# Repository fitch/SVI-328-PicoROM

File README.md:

# SVI-328 PicoROM

## Overview

SVI-328 PicoROM is a ROM emulator for Spectravideo 328 which uses a [Raspberry Pico 2 W](https://www.raspberrypi.com/products/raspberry-pi-pico-2/) microcontroller board to emulate a SVI-328 game ROM cartridge.

Designed to integrate into the conventional cartridge slot of the SVI-328, this cartridge allows wireless transmission of ROM games from macOS/PC to the SVI-328 via Wi-Fi without any hardware modifications.

## Repository contents

This repository contains:

 - C firmware source code ([pico](pico/) directory) for Raspberry Pi Pico 2 W responsible for dynamic ROM emulation and wireless data transfer.
 - PCB design files ([pcb](pcb/) directory), including schematics and layouts, developed using KiCad, suitable for fabrication with, for example, [PCBWay](https://www.pcbway.com/).
 - Node.js JavaScript-based utility ([send_rom.js](js/send_rom.js)) designed for remote ROM image transmission via WiFi.
 - Z80 assembly language code ([rom](rom/) directory) constituting the boot-up ROM launcher, facilitating initial system configuration and operational initialization.

## How to get it running quickly

### Cartridge hardware

First, create the PCB by ordering it from [PCBWay](https://www.pcbway.com/) with the Gerber files provided in [release/svi-328-picorom-gerber.zip](release/svi-328-picorom-gerber.zip).

Then get a [Raspberry Pico 2 W](https://www.raspberrypi.com/products/raspberry-pi-pico-2/) (not the version 1, and make sure you order the Wi-Fi version W) and one atleast +5V diode (DigiKey part number 4878-1N4001CT-ND DIODE GEN PURP 50V 1A DO204AC works, for example).

Solder these together. :) 

### Cartridge software

Press Pico's BOOTSEL button (the only button on the board, see the board picture above) and while pressing plug it in to your computer via USB.

Then, find the UF2 flash binary file from [release/svi-328-picorom.uf2](release/svi-328-picorom.uf2).

Next, flash the Raspberry Pico 2 W by dragging the UF2 file on to the Pico USB drive and wait until Pico disconnects (displays `Disk Not Ejected Properly` in macOS) and the green LED light turns on to signal that the firmware booted correctly. Finally, remove the USB cable.

### Booting up and sending a ROM

Connect the cartridge to SVI-328 and boot it up. (Warning: **DO NOT** connect anything to the cartridge USB port when it is attached to the SVI-328. This will destroy the cartridge.)

If you didn't flash the Wi-Fi credentials (see section [Flashing Wi-Fi credentials to the cartridge](#flashing-wi-fi-credentials-to-the-cartridge)), the SVI-328 should ask for your Wi-Fi SSID and password. Please note, that once you store successfully working credentials, there is no way (currently) to remove the stored credentials using SVI-328. You need to use the command line utility described in section [Flashing Wi-Fi credentials to the cartridge](#flashing-wi-fi-credentials-to-the-cartridge).

The SVI-328 will remain waiting for a client.

To send a ROM from Windows or macOS, use the `send_rom.js` to send it. It should display the following information:
```
node js/send_rom.js Boulder\ Dash-MSX-to-SVI.rom 
Waiting for SVI-328 at address 0.0.0.0...
Connecting to SVI-328 at 192.168.1.100...
Connected. Sending ROM upload command...
ROM sent. Listening for logs:
```

After this, the SVI-328 should boot to the sent ROM.

**NOTE**: Only 32 kB ROM images are supported at the moment.

## System prerequisites

The replication and deployment of this project requires the following environment configurations:
 - Raspberry Pi Pico SDK installation and associated toolchains.
 - Node.js runtime environment for executing the provided WiFi-based ROM transmission scripts.
 - KiCad for PCB customization, schematic evaluation, and Gerber file generation.

The build scripts have been developed and tested with macOS Sonoma 14.6.1 and requires the following software to be installed:

 - [Visual Studio Code](https://code.visualstudio.com) 1.98.2 or newer 
 - Raspberry Pico Visual Studio Code extensions with [these](https://www.raspberrypi.com/news/get-started-with-raspberry-pi-pico-series-and-vs-code/) instructions
 - picotool 2.1.1, `brew install picotool` with [HomeBrew](https://brew.sh)
 - [z88dk version 2.3](https://github.com/z88dk/z88dk) (currently only z88dk-z80asm is used)
 - [openMSX emulator version 20.0](https://openmsx.org/) (which should be installed in /Applications/openMSX.app)
 - [Node.js version 22.12.10](https://nodejs.org/en) or newer
 - [Node Version Manager 22.12.0](https://github.com/nvm-sh/nvm) or newer (it's easier to manage Node versions with this, but you can omit this you install Node.js some other way)
 - [KiCad version 8.0.6](https://www.kicad.org/download/) or newer

## SVI-318 compatibility

The hardware will work with SVI-318 and the loader software should also work with it, altough it has not been tested on a real device yet.

## Compiling the source code

### The launcher ROM source code for SVI-328

The launcher ROM code is in [rom](rom/) directory and you can compile with the following commands:

```
nvm use
make production
```

This will create the ROM binary and the includable rom.h (for the next step) in `release` directory. Copy the `rom.h` to `pico` directory for the next step:

```
cp release/rom.h ../pico/
```

### Raspberry Pico 2 W firmware source code

The Pico firmware source code is located in [pico](pico/) directory and you can compile it by opening the folder in Visual Studio Code. First time, if you have installed the Visual Studio Code extensions, VSCode will install the Pico SDK and then you can click the `Compile` button in the bottom bar.

If you have the cartridge connected via USB, you can use the `Run` button to flash the firmware directly to the cartridge. Another option is to get the UF2 file from the `build` directory, see section [How to get it running quickly](#how-to-get-it-running-quickly).

### Flashing Wi-Fi credentials to the cartridge

You can flash your Wi-Fi credentials to the cartridge to save some valuable typing time on SVI-328, altough I suggest that you take the time to enjoy the never-seen-before experience to enter SSID and the Password on your Spectravideo 328. :) 

Using the example `wifi-credentials.config.example`, create a `wifi-credentials.config` to the root of the project. Then connect the cartridge via USB and flash the credentials:

```
scripts/write_credentials.sh
```

To remove stored credentials, use this command:

```
scripts/write_credentials.sh --clear
```

## Operational framework

### Firmware architecture (Raspberry Pi Pico 2 W)

The firmware executed by the Raspberry Pi Pico 2 W addresses two critical operational roles:

1. **ROM memory emulation**:

    The microcontroller interfaces directly with the SVI-328's cartridge slot to emulate ROM data storage. ROM contents are dynamically allocated and retrieved from the internal memory of the Pico.

2. **WiFi-Based ROM data transmission**:

    ROM images are transmitted wirelessly to the Pico via WiFi. A dedicated JavaScript utility (`send_rom.js`) facilitates the transfer and concurrently provides logging capabilities for debugging and operational monitoring.

The firmware source comprises:

 - `main.c`: Responsible for system initialization, WiFi configuration, and reception and handling of ROM data.
 - `wifi.c/h`: Manages WiFi connectivity, session handling, and data exchange between the Pico and external hosts.
 - `svi-328-cartridge.c/h`: Implements the logic necessary for cartridge ROM emulation.
 - `log.c/h`: Provides logging utilities essential for debugging and real-time data monitoring.

### Hardware design and PCB layout

The project hardware consists of a specialized PCB that integrates the Raspberry Pi Pico W and essential connectors for direct communication with the Spectravideo 328:

 - Edge Connector: Engineered for direct compatibility with the standard SVI-328 cartridge interface.
 - Raspberry Pi Pico W Module: Manages operational logic for ROM emulation and wireless communication protocols.

### Communication between SVI-328 and Pico

The Pico-based cartridge presents itself to the SVI-328 as a memory-mapped ROM with additional control registers in the cartridge address space. The SVI-328 accesses the Pico’s “ROM” as if it were a normal cartridge memory, using the address range 0x0000–0x7FFF when the cartridge is enabled. The Pico’s firmware uses the RP2350’s GPIO to monitor the SVI’s address and control lines and to drive or sample the data bus accordingly:

 - ROM Data Window (0x0000–0x3FFF): When the SVI reads from the lower 16KB of the cartridge space, the Pico responds with byte data from an emulated ROM. On reset, this window contains the boot loader and launcher code. Later, once a game is loaded, this window is updated to expose the game’s ROM data for the SVI to fetch. The Pico monitors the /CCS1 signal (chip-select for 0x0000–0x3FFF) to detect these accesses and output the correct data bytes from its internal memory buffer.
 - Upper ROM Data Window and Control/Status Registers (0x4000–0x7FFF): The upper 16KB of the cartridge space is repurposed as a communication interface. The Pico firmware distinguishes accesses to this range via the /CCS2 signal (chip-select for 0x4000–0x7FFF) and does not treat them as normal ROM reads. Instead, certain addresses in this range act as pseudo-registers for handshaking:
    - 0x7FFF – Pico Status Register: Reading from address 0x7FFF returns a state code byte indicating the Pico’s current status (described below). The SVI’s launcher program polls this address to know what the Pico is doing (e.g., waiting for data, busy, ready, etc.).
    - To prevent accidental writes, the launcher uses an unlock sequence: the SVI must perform a specific sequence of dummy reads from three “signature” addresses (defined in the firmware) before the Pico will accept writes to 0x7F00–0x7F02.
    - 0x7F00 & 0x7F01 – Data Write State Registers: Reading to these addresses allows the SVI to send data to the Pico. In this project, they are used to transmit WiFi credentials (e.g., SSID and password) or other input to the Pico.
    - 0x7F02 – Termination Register: Reading address 0x7F02 signals the end of an input string (used to indicate that the full SSID or password has been sent). This lets the Pico know it has received the complete data item.
    - 0x7F00 - 0x7FFF Data to be transmitted: Reading these addresses will translate to the bytes sent by SVI to Pico.

## Special thanks

This project is based on [A8PicoCart](https://github.com/robinhedwards/A8PicoCart), [PiCOLECO](https://github.com/aotta/PiCOLECO) and learnings from [SVI-328 MegaROM](https://github.com/fitch/SVI-328-MegaROM).

## License

Detailed licensing information is documented within the included [LICENSE](LICENSE) file.

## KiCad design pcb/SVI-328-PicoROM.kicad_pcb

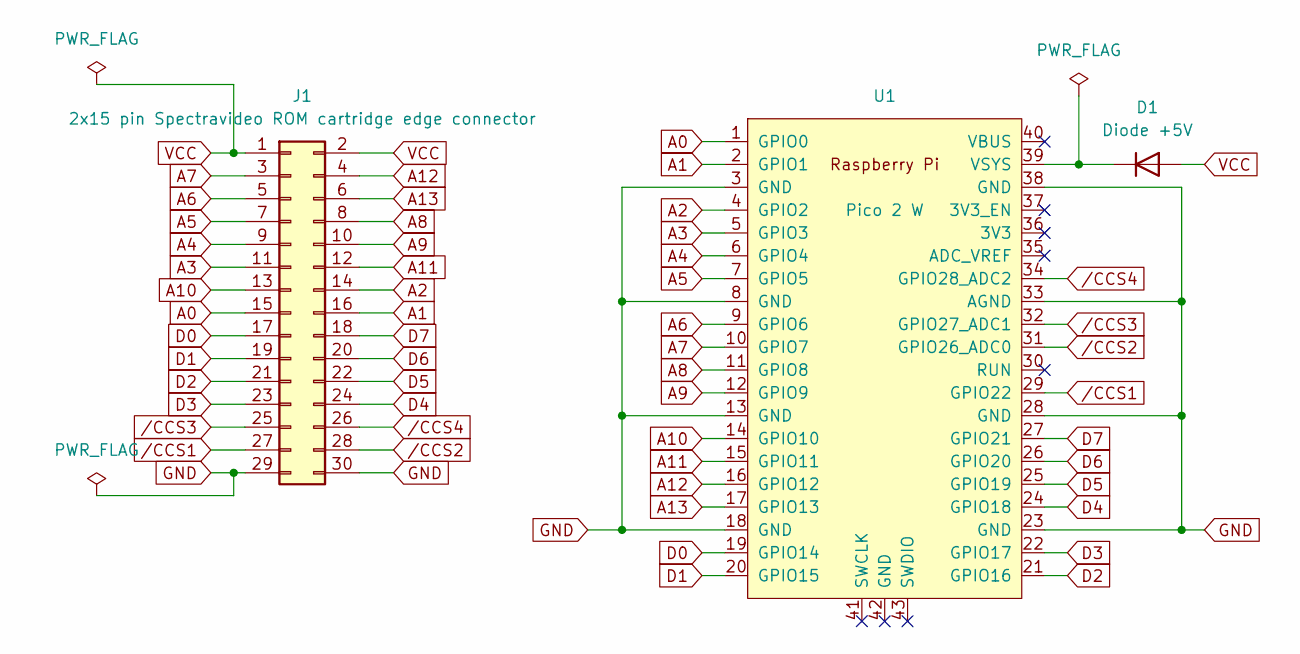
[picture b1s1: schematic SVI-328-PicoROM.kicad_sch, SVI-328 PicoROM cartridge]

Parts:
D1: Diode +5V; D_DO-35_SOD27_P7.62mm_Horizontal
J1: 2x15 pin Spectravideo ROM cartridge edge connector; ROM cartridge edge connector
U1: Pico 2 W; RPi_PicoW_SMD_TH

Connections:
A0: J1.15, U1.1 (GPIO0)
A1: J1.16, U1.2 (GPIO1)
A2: J1.14, U1.4 (GPIO2)
A3: J1.11, U1.5 (GPIO3)
A4: J1.9, U1.6 (GPIO4)
A5: J1.7, U1.7 (GPIO5)
A6: J1.5, U1.9 (GPIO6)
A7: J1.3, U1.10 (GPIO7)
A8: J1.8, U1.11 (GPIO8)
A9: J1.10, U1.12 (GPIO9)
A10: J1.13, U1.14 (GPIO10)
A11: J1.12, U1.15 (GPIO11)
A12: J1.4, U1.16 (GPIO12)
A13: J1.6, U1.17 (GPIO13)
D0: J1.17, U1.19 (GPIO14)
D1: J1.19, U1.20 (GPIO15)
D2: J1.21, U1.21 (GPIO16)
D3: J1.23, U1.22 (GPIO17)
D4: J1.24, U1.24 (GPIO18)
D5: J1.22, U1.25 (GPIO19)
D6: J1.20, U1.26 (GPIO20)
D7: J1.18, U1.27 (GPIO21)
GND: J1.29, J1.30, U1.3 (GND), U1.8 (GND), U1.13 (GND), U1.18 (GND), U1.23 (GND), U1.28 (GND), U1.33 (AGND), U1.38 (GND)
unnamed: D1.1 (K), U1.39 (VSYS)
VCC: D1.2 (A), J1.1, J1.2
/CCS1: J1.27, U1.29 (GPIO22)
/CCS2: J1.28, U1.31 (GPIO26_ADC0)
/CCS3: J1.25, U1.32 (GPIO27_ADC1)
/CCS4: J1.26, U1.34 (GPIO28_ADC2)

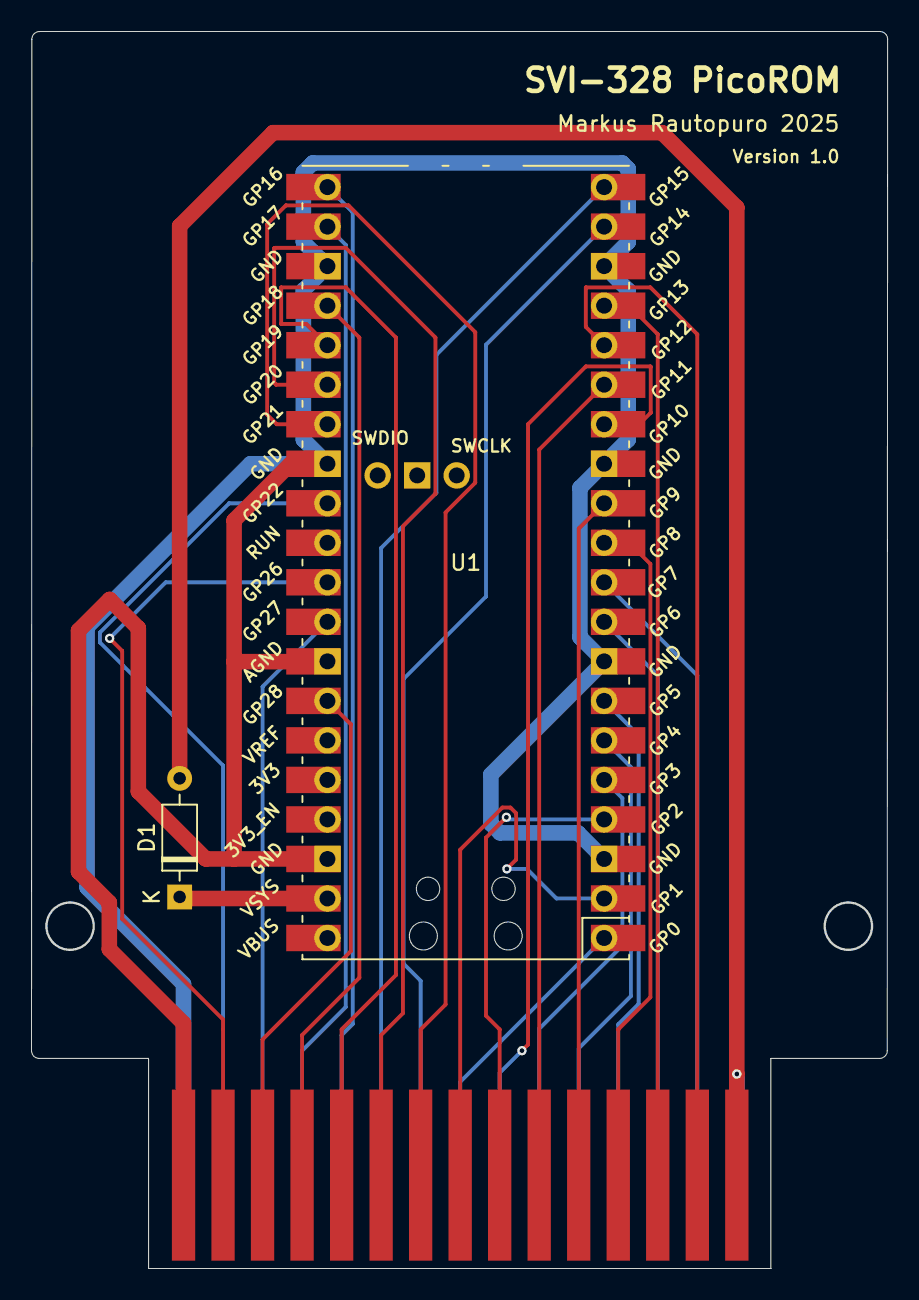
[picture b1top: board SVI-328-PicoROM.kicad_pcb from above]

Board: 2 copper layers, 54.9 x 79.4 mm, 3 parts (0 on the bottom side), 29 nets.

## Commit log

2025-04-04 First working version
2025-04-06 Fix README.md
